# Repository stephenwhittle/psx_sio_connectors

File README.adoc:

:toc:
:toclevels: 2

[discrete]
= DIY PSX SIO Adaptors/Connectors

This repository contains 3D models and PCB footprints/layouts for making your own connectors suitable for interfacing with the serial port (SIO) of Playstation 1 consoles. This port uses a proprietary connector and no off-the-shelf options are currently available. As a result, we have to DIY our own connectors, a number of options for which are documented here.

== Cheapest, hackiest option (If you have (but dont want to butcher) a link cable) - aka the 'SOIC port'

image::img/20250620_124839.jpg[alt="two SOIC adaptors cut into the correct shape with contacts and pin headers, ready for use",width=400, link=https://github.com/stephenwhittle/psx_sio_connectors/blob/main/img/20250620_124839.jpg]

The pin spacing of the contacts in this connector, as best I can tell, is 1.24mm and pads are approx 0.62mm wide. 
As a result, any SOIC-16 to DIP adaptor PCB can be cut down to size. SOIC leads have a 1.27mm pitch, but across 8 contacts there won't be enough accumulated drift to result in pins shorting out or making contact incorrectly.

image::img/20250620_131232.jpg[alt="a SOIC to DIP breakout with red lines indicating which portions of the PCB should be trimmed away", width=400, link=https://github.com/stephenwhittle/psx_sio_connectors/blob/main/img/20250620_131232.jpg]

Note, when making the vertical cuts on this image, you may wish to leave a little extra FR4 there and then file the sides down to ensure a snug fit and easy alignment of contacts once they are soldered on.

Solder some 0.5mm diameter wire across each of the pairs of contacts, or alternatively use some pins pulled from vertical 0.1" headers, a much easier option as the square profile of those pins will stop them rolling around as you solder. The fact that the pins won't roll around so much also makes it trivial to just reflow the board with  a hotplate if you have one.

Once you have soldered the wires or pins, place a small piece of Kapton or other tape on the underside to avoid shorting across the metal body of the cable, and solder some 0.1" right-angle header pins to the 8 remaining plated through-holes, and you are ready to go.

image:img/20250620_133311.jpg[alt="a SOIC to DIP adaptor with individual copper wires soldered across the SOIC leads, connected to a PSX link cable so that the right-angle header on the other side of the adaptor is exposed for use", height=250, float=left, link=https://github.com/stephenwhittle/psx_sio_connectors/blob/main/img/20250620_133311.jpg]
image:img/20250620_133352.jpg[alt="a SOIC to DIP adaptor with 0.1 inch header pins soldered across the SOIC leads, connected to a PSX link cable so that the right-angle header on the other side of the adaptor is exposed for use", height=250, float="right",link=https://github.com/stephenwhittle/psx_sio_connectors/blob/main/img/20250620_133352.jpg]

It's worth pointing out that this relies on the fact that the link cable has embedded spring contacts, so we don't need to worry too much about getting enough height out of the impromptu contacts we've soldered onto the PCB. However we do need to use wire thats at least 0.5mm thick to ensure that the spring contacts will, well, contact.

== If you have a 3d printer, but no link cable, and are too impatient to wait for PCBs

image:img/stl_render.png[alt="a render of a 3d printed connector which acts as a form for wires that will make contact with the internal SIO connector of the playstation", width=400,link=https://github.com/stephenwhittle/psx_sio_connectors/blob/main/img/stl_render.png]

Instead of cutting and filing a PCB down to size, another option is to 3d print a form/holder for some wires that gives them an appropriate profile to reach the contacts inside the internal SIO connector on the console itself. This repository contains an OpenSCAD script and STL file for such a form, suitable for printing on an FDM printer (will probably work on DLP/resin printers as well, but I haven't tested those).

This connector is based on the work done over at https://github.com/hornc/psx-serial-expts .

The original design was intended for use by connecting to the end of an intact link cable in the same fashion as the 'SOIC port' presented above. I have modified it in the following ways so that it can connect into the console directly instead:

* Tweaks to better accommodate 0.4mm wire being used for the contacts
* The addition of a protoboard mounting plate at the back of the connector
* The addition of a ridge internally which guides the wire so that it bends appropriately to make contact with the SIO port's internal contacts

Once the connector is printed, run 0.4mm copper wire through the channels as indicated in this picture, and then solder that to a perfboard with 0.1" header, ready for connection to your USB<->serial adaptor. I used PU-coated copper wire, hence having to tin the front portion of each wire to burn that insulation off. 

image:img/20250620_124911.jpg[alt="a 3d printed piece of plastic with a number of copper wires inserted into it which form electrical contacts. The plastic is screwed onto a 20x80mm protoboard, and the copper wires are threaded into the protoboard and soldered onto 0.1 inch pin headers", width=400,link=https://github.com/stephenwhittle/psx_sio_connectors/blob/main/img/20250620_124911.jpg]

The mounting plate and screw holes are appropriately spaced for connection to the standard 20x80mm protoboards commonly found on Aliexpress, which you could cut down to size. You could make a more compact version of this design by only breaking out the TXD/RXD/GND signals to pin headers, too.

image:img/20250620_150013.jpg[alt="The printed connector and attached protoboard, connected to a Playstation with three jumper leads running off of it", width=400, link=https://github.com/stephenwhittle/psx_sio_connectors/blob/main/img/20250620_150013.jpg]

== (More) 'Expensive' but reliable: SIO Connector PCB

image:img/footprint.png[alt="footprint of the connector with dimensions for pads", float=left, height=310, link=https://github.com/stephenwhittle/psx_sio_connectors/blob/main/img/footprint.png]
image:protoboard/board.png[alt="Screenshot from Diptrace showing the adaptor PCB", float=right, width=350, link=https://github.com/stephenwhittle/psx_sio_connectors/blob/main/protoboard/board.png]

Based on the 'SOIC port', this repository also contains the design files and gerbers for a footprint and connector PCB that can directly plug into the SIO port. 

The board can be ordered from JLCPCB for about $8 for 5 boards, even if panelled 3x3 to a board so you get plenty of adaptors to experiment with:

image:img/20250620_131156.jpg[alt="PCBs in a 3x3 panel, separated by v-scores that have not been snapped apart yet", width=400, link=https://github.com/stephenwhittle/psx_sio_connectors/blob/main/img/20250620_131156.jpg]

In order to use the footprint, wire must be soldered to the contacts, with the total combined height of board and wires needing to be about 2.5-2.6mm. The internal connector in the Playstation has plastic ridges on either side of each contact, so the wire used should be no more than 0.6mm wide. However, when adding 0.6mm to a standard 1.6mm PCB, the combined height is only 2.2mm meaning that your wires will not contact the internal connector correctly. 

For this reason, if you are using 1.6mm PCBs, you will need to double your wire up on itself like the following image:

image:img/20250620_171634.jpg[alt="a piece of PU coated copper wire doubled up on itself with a very tight bend",width=400, link=https://github.com/stephenwhittle/psx_sio_connectors/blob/main/img/20250620_171634.jpg]

Solder these wires together to form a single 0.5mm x 1mm piece: 

image:img/20250620_172101.jpg[alt="the same wire with solder covering the two strands, holding them together",width=400, link=https://github.com/stephenwhittle/psx_sio_connectors/blob/main/img/20250620_172101.jpg]

Then solder that to the pcb so that the long edge is perpendicular to the board.

With your wires firmly attached to the breakout, measure the thickness across the tallest portion of your wire contacts, and file the wires down until you have a height of approximately 2.6mm or slightly less.

image:img/20250620_172402.jpg[alt="a piece of PU coated copper wire doubled up on itself with a very tight bend",width=400, link=https://github.com/stephenwhittle/psx_sio_connectors/blob/main/img/20250620_172402.jpg]

=== Usage Examples

The PCB breaks the 8 contacts from the SIO port out to the row of 0.1" headers closest to the console. You can solder header pins to that row and directly connect a USB<->serial cable, or use some additional wires to relocate the header pins elsewhere on the mini-protoboard:

image:img/20250620_124939.jpg[alt="a circuit board showing three wires soldered to contacts on the board and some copper wire between those contacts and pin headers", float=left, height=300, link=https://github.com/stephenwhittle/psx_sio_connectors/blob/main/img/20250620_124939.jpg]
image:img/20250620_165220.jpg[alt="the circuit board connected to the SIO port of a playstation with three Dupont leads connected to pin headers", float=right, height=300, link=https://github.com/stephenwhittle/psx_sio_connectors/blob/main/img/20250620_165220.jpg]

The protoboard area contains pads at 1.27mm intervals, suitable for the placement of a microcontroller or other interface chip in either DIP, or SOIC packages, if you want to build a standalone adaptor that plugs directly into a USB port with bare wires.
The protoboard footprint's pad design is a recreation of the pattern found in https://github.com/electroniceel/protoboard .

Pictured here is a WCH CH343G connected to the protoboard with a USB cable attached:

image:img/20250620_125129.jpg[alt="a circuit board showing some wires soldered to contacts and a USB cable connected to header pins",float=left, height=300, link=https://github.com/stephenwhittle/psx_sio_connectors/blob/main/img/20250620_125129.jpg]
image:img/20250620_125151.jpg[alt="the opposite side of the circuit board showing an IC with copper wire connected to the pins",float=right, height=300, link=https://github.com/stephenwhittle/psx_sio_connectors/blob/main/img/20250620_125151.jpg]

image:img/20250620_125030.jpg[alt="the adaptor PCB with CH343G IC connected to the serial port of the console", width=600, link=https://github.com/stephenwhittle/psx_sio_connectors/blob/main/img/20250620_125030.jpg]

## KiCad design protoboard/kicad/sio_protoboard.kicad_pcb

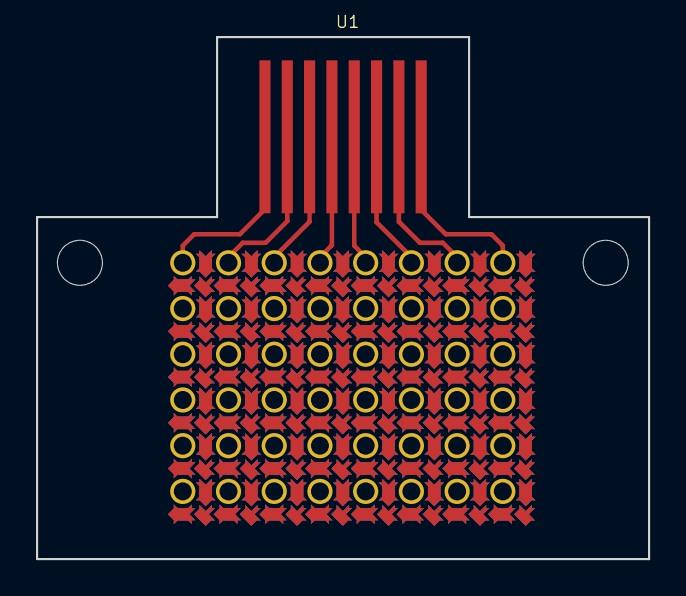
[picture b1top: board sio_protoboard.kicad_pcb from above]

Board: 2 copper layers, 34.0 x 29.0 mm, 9 parts (0 on the bottom side), 8 nets.

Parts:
U1: SIO_062X10; SIO_062x10
U2, U3, U4, U5, U6, U7: ROW_1X8_LP_2SIDED; Row_1x8_LP_2Sided
UNK_HOLE_0: dummyfp0
UNK_HOLE_1: dummyfp1

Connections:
Net_0: U1.4, U7.4
Net_1: U1.5, U7.5
Net_2: U1.3, U7.3
Net_3: U1.2, U7.2
Net_4: U1.1, U7.1
Net_5: U1.6, U7.6
Net_6: U1.7, U7.7
Net_7: U1.8, U7.8
